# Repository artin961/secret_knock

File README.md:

#SECRET KNOCK DETECTING DOOR LOCK

The circuit is based around ATTiny85 MCU. 
It can be powered from 8-16VDC becouse it has onboard linear regulator. 
It uses N Channel mosfet to triger solenoid lock.
There is an option to unlock the door via external positive signal via the optocoupler.

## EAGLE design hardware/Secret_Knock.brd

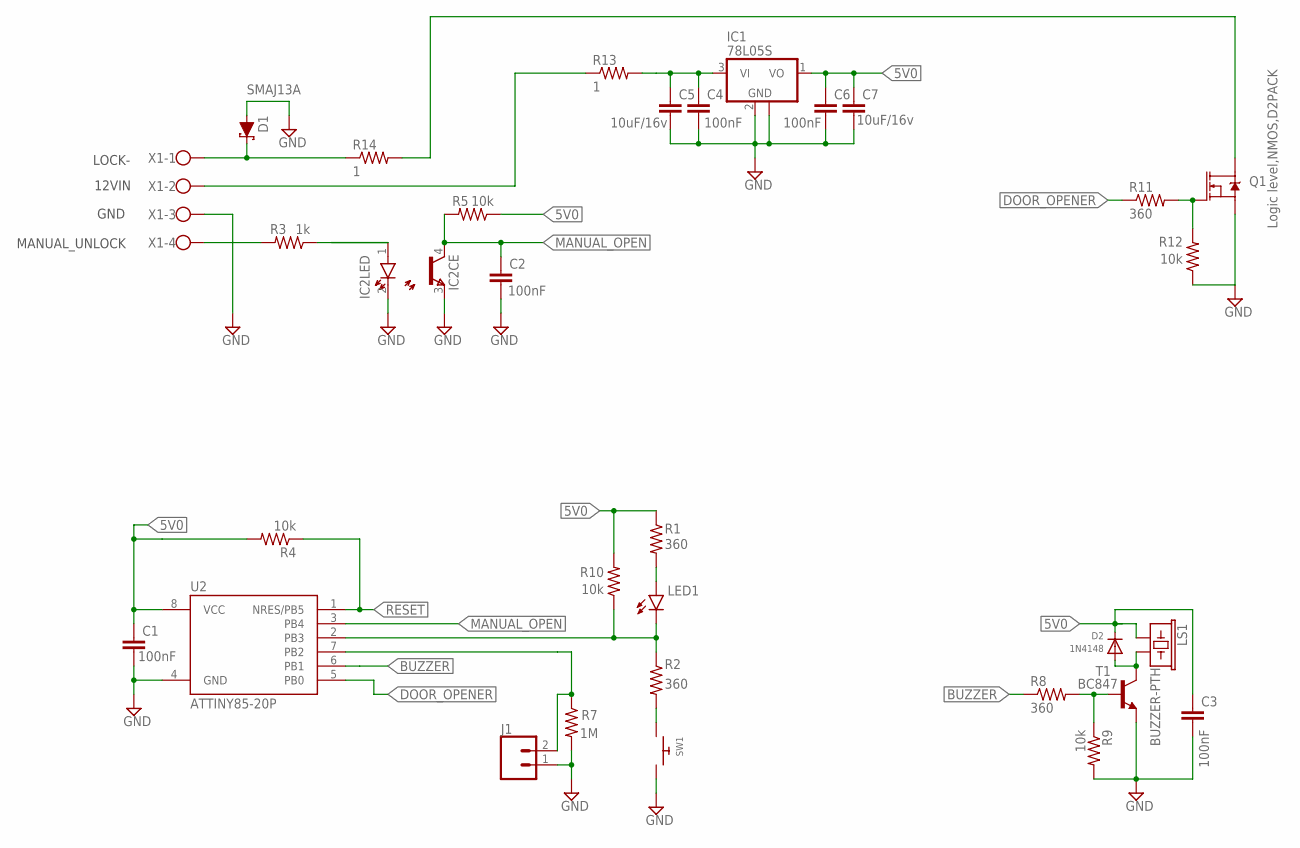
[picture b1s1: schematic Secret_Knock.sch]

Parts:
C1, C2, C3, C4, C6: 100nF; C0805
C5, C7: 10uF/16v; C0805
D1: SMAJ13A; SMA-DIODE
D2: 1N4148; SOD-123
IC1: 78L05S; SOT89
IC2: GENERIC OPTOCOUPLER, PC817; SFH
J1: CONN_02POLAR_LOCK; MOLEX-1X2_LOCK
LED1: LEDSML0805; SML0805
LS1: BUZZER-PTH; BUZZER-12MM
Q1: Logic level,NMOS,D2PACK; TO-263/D2PAK
R1, R2, R8, R11: 360; R0805
R3: 1k; R0805
R4, R5, R9, R10, R12: 10k; R0805
R7: 1M; R0805
R13, R14: 1; R0805
SW1: SWITCH_PUSHBUTTONEVQ-PE; TACT_PANA-EVQ
T1: BC847; SOT23
U2: ATTINY85-20P; PDIP08_300MIL
X1: W237-4

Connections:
5V0: C1.1, C3.1, C6.1, C7.1, D2.C, IC1.1 (VO), LS1.+ (1), R1.1, R4.2, R5.1, R10.2, U2.8 (VCC)
BUZZER: R8.1, U2.6 (PB1)
DOOR_OPENER: R11.1, U2.5 (PB0)
GND: C1.2, C2.2, C3.2, C4.2, C5.2, C6.2, C7.2, D1.A, IC1.2 (GND), IC1.2@1 (GND), IC2.2 (K), IC2.3 (E), J1.1, Q1.3 (S), R7.2, R9.2, R12.1, SW1.P$2, T1.2 (E), U2.4 (GND), X1.3
MANUAL_OPEN: C2.1, IC2.4 (C), R5.2, U2.3 (PB4)
unnamed: Q1.2 (D), R14.2
unnamed: LED1.A, R1.2
unnamed: R2.2, SW1.P$1
unnamed: LED1.C, R2.1, R10.1, U2.2 (PB3)
unnamed: R3.2, X1.4
unnamed: IC2.1 (A), R3.1
unnamed: D2.A, LS1.- (2), T1.3 (C)
unnamed: R8.2, R9.1, T1.1 (B)
unnamed: Q1.1 (G), R11.2, R12.2
unnamed: R13.1, X1.2
unnamed: D1.C, R14.1, X1.1
unnamed: C4.1, C5.1, IC1.3 (VI), R13.2
PIEZO_IN: J1.2, R7.1, U2.7 (PB2)
RESET: R4.1, U2.1 (NRES/PB5)

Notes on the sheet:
LOCK-
12VIN
GND
MANUAL_UNLOCK

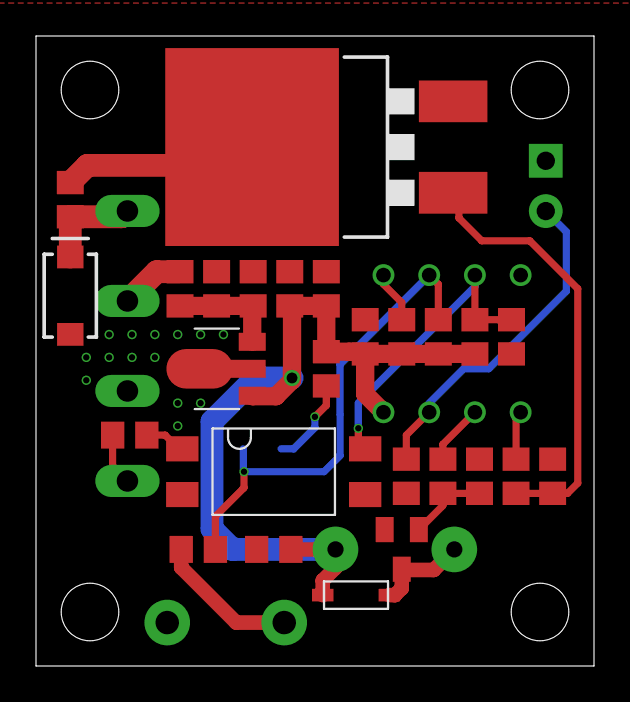
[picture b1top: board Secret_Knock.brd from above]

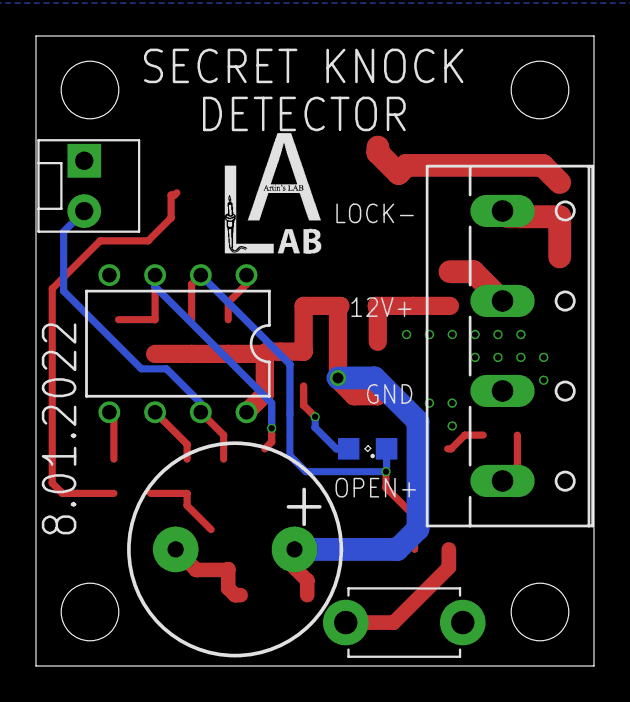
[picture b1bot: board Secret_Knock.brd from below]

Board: 2 copper layers, 31.0 x 35.0 mm, 33 parts (7 on the bottom side), 19 nets.

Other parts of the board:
U$1: ALAB_LOGO

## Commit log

2022-06-17 Added README
2023-08-24 schematic and board file added

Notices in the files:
parts and their libraries:
SparkFun-DiscreteSemi: Licensing: Creative Commons ShareAlike 4.0 International - https://creativecommons.org/licenses/by-sa/4.0
